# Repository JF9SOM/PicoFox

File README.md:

# PicoFox – A Hackable 2m Fox Transmitter

**PicoFox** is an open source fox transmitter for the 2-meter amateur band, built around the
RP2040 microcontroller (the same chip used in the Raspberry Pi Pico). It’s designed to be simple,
functional, and easy to modify.

PicoFox works well as a standalone fox for portable or walking hunts, but it’s also a great platform
for experimentation. There's ample CPU, flash, and GPIO available if you want to add features like
sensors or interactivity. The transmitter can generate a frequency or phase modulated signal with up
to 2.5kHz (data) bandwidth.

## Key Features
- Transmits FM in the 144–148 MHz band (ITU Zone 1: 144–146 MHz).
- Configured by editing a text file — no software or terminal needed.
- Transmits any 5kHz 16-bit PCM WAV file.
- Automatic Morse code ID with configurable tone, speed, and spacing.
- RF output > 18dBm at full power. Down to ~ -20dBm with full attenuation.
- Charges over USB.
- Expansion header provides:
  - 12 GPIOs (including I2C, SPI, UART, ADC).
  - Regulated 3.3V and raw battery voltage.
  - Two additional SI5351 clock outputs

### Getting One

Fully assembled PicoFox units are available from [AI6YM.radio](https://ai6ym.radio/picofox). An
enclosure, battery, and antenna are included. I ship nearly anywhere in the world.

You can also build your own - both the hardware and software are open source for non-commercial use.
For commercial inquiries, contact [justin@ai6ym.radio](mailto:justin@ai6ym.radio).

## Configuration

To configure your PicoFox, connect it to any computer using a micro USB cable. It will appear as a
USB mass storage device (like a flash drive). Open `settings.txt` with a text editor and adjust the
configuration values as needed. Eject the drive, disconnect USB, and power cycle the PicoFox to
apply the new settings.

To reset to factory settings, delete `settings.txt`, eject the drive, disconnect USB, and power
cycle the PicoFox. A default settings file will be regenerated.

### Settings Overview

- `CALLSIGN`: Alphanumeric callsign (max 12 characters).
- `ITU_ZONE`: ITU zone where the transmitter operates (`1`, `2`, or `3`).
- `FREQ_MHZ`: Transmit frequency in MHz.
- `ATTENUATION`: Attenuation level `0` - `127`, approximately 0.25dB steps.
- `DUTY_CYCLE`: Transmit duty cycle percentage (`0–100`).
- `MORSE_WPM`: Morse ID speed in words per minute.
- `MORSE_FARNSWORTH_WPM`: Slower Farnsworth spacing speed (ignored if lower than `MORSE_WPM`).
- `MORSE_TONE`: Morse tone frequency (100–2000 Hz).
- `MORSE_TONE_VOL`: Morse tone volume percentage (`1–100`).

**Note:** Invalid or missing values may disable the transmitter or revert to safe defaults.

## Using the Transmitter

After configuring settings as described above. The transmitter will turn on following the
provided settings the next time it is turned on.

The transmitter may be powered by an external USB power supply or the internal battery. The internal
battery charges over USB but no indication is available to show battery charging.

**Note: The power switch must be ON to charge the battery over USB. The transmitter will run on USB
power with the switch OFF but the battery will NOT be charged.**

A full battery will last about five hours at 100% duty cycle, 

## Replacing the Audio File

To change the audio transmission, replace the `audio.wav` file in the device’s flash storage. The
audio must be sampled at **5kHz**, **mono** (one channel), and encoded as **signed 16-bit PCM WAV**.

Using **Audacity** (free software available for all major OSs):

1. Set "Project Rate (Hz)" to `5000`.
2. Import, record, or generate your audio.
3. Mix down to a single mono track.
4. Export as WAV using **Signed 16-bit PCM** encoding.
5. Name the file `audio.wav` and copy it to the device.
6. Eject the drive and disconnect USB.
7. Power cycle the PicoFox.

**Notes:**

- Improper format may prevent audio transmission or cause noise to be transmitted instead.
- The audio is transmitted, followed by the morse ID, and then the transmitter turns off if
  `DUTY_CYCLE < 100`. In this way the length of the audio determines the transmit cycle time and the
  frequency of morse code ID transmissions. **YOU ARE RESPONSIBLE FOR COMPLYING WITH LOCAL LAWS FOR
  TRANSMITTING YOUR CALLSIGN!**
- To restore the default audio, delete `audio.wav`, eject the drive, disconnect USB, and power cycle
  the PicoFox.

## Design Brief

An SI5351 clock generator, locked to a TCXO, provides the RF signal. Modulation is applied in
software by the RP2040. To achieve smooth FM output, modulation is handled on core 1 with
I<sup>2</sup>C running at 1 MHz. Register writes are minimized and no other devices are on
I<sup>2</sup>C0.

Core 0 manages flash operations. Most extensions or new features should run on core 0.

**Note:** Mounting the device as a USB mass storage device will interrupt clean modulation as both
cores are blocked during flash operations.

The SPI flash device is split into program memory and a FAT16 filesystem. The filesystem contains
a text file for user-supplied settings, an audio file for transmission, a second audio file
containing the generated morse code ID, and a hash file used to detect changes to the settings file.
Unexpected files are automatically deleted and missing files are re-created from defaults in the
firmware binary.

The design intentionally includes large amounts of free CPU cycles, RAM, and flash so that cool
things can be built on the PicoFox.

## Development Guide

### Build Environment Setup

- Install Arduino IDE >= 2.3.
- Install libraries - Adafruit SPIFlash, Adafruit TinyUSB, Etherkit Si5351.
- Install board package from [my fork of Arduino-Pico](https://github.com/ai6ym/arduino-pico). This
  will be merged upstream eventually but for now you'll need the changes in my fork.
- In `Tools -> Board` select the `Raspberry Pi RP2040/RP2350 Boards -> AI6YM PicoFox`.
- Connect your PicoFox and select the appropriate TTY / COM port.

On Linux it may be necessary to add udev rules for this device. The relevant rules from my system
are below. I have no idea how this works on other operating systems. Mac is probably similar,
Windows should not be used for software developement of any kind (or really anything).

```
# Make an RP2040 in BOOTSEL mode writable by all users, so you can `picotool`
# without `sudo`. 
SUBSYSTEM=="usb", ATTRS{idVendor}=="2e8a", ATTRS{idProduct}=="0003", MODE="0666"

# Symlink an RP2040 running MicroPython from /dev/pico.
#
# Then you can `mpr connect $(realpath /dev/pico)`.
SUBSYSTEM=="tty", ATTRS{idVendor}=="2e8a", ATTRS{idProduct}=="0005", SYMLINK+="pico"

# Adafruit TinyUSB stack.
SUBSYSTEM=="tty", ATTRS{idVendor}=="239a", ATTRS{idProduct}=="cafe", MODE="0666"
SUBSYSTEM=="usb", ATTRS{idVendor}=="239a", ATTRS{idProduct}=="cafe", MODE="0666"
```

### Compilation Settings

- `Flash Size`: `16MB (Sketch: 1MB, FS: 15MB)`
- `CPU Speed`: `TBD`
- `USB Stack`: `Adafruit TinyUSB`

If needed for some reason you could change the partition layout to give more space for the sketch.
Doing so would destroy all data but the code automatically formats the partition and writes
defaults.

All other settings are fine at default values.

### Recovering a Board

In general the UF2 upload process will work fine. Click the upload button, after compilation the IDE
will push the board into UF2 update mode, write the new binary, and then reset the board to normal
operation.

If that doesn't work try the following:
- Reset the board and try again. Just tap the `RESET` button on the board to reset the RP2040.
- Force the device into `BOOTSEL` mode. Hold the `BOOTSEL` button, tap the `RESET` button, and then
  release the `BOOTSEL` button.
- Force the device into `BOOTSEL` mode **AND** change `Tools -> Upload Method` to `PicoTool`.
- When all else fails grab a PicoProbe (or a Pico / Pico2 flashed with the PicoProbe binary),
  connect that to the debug header of the PicoFox, and change `Tools -> Upload Method` to
  `Picoprobe`.
- If all of the above fails, well, he's dead Jim.

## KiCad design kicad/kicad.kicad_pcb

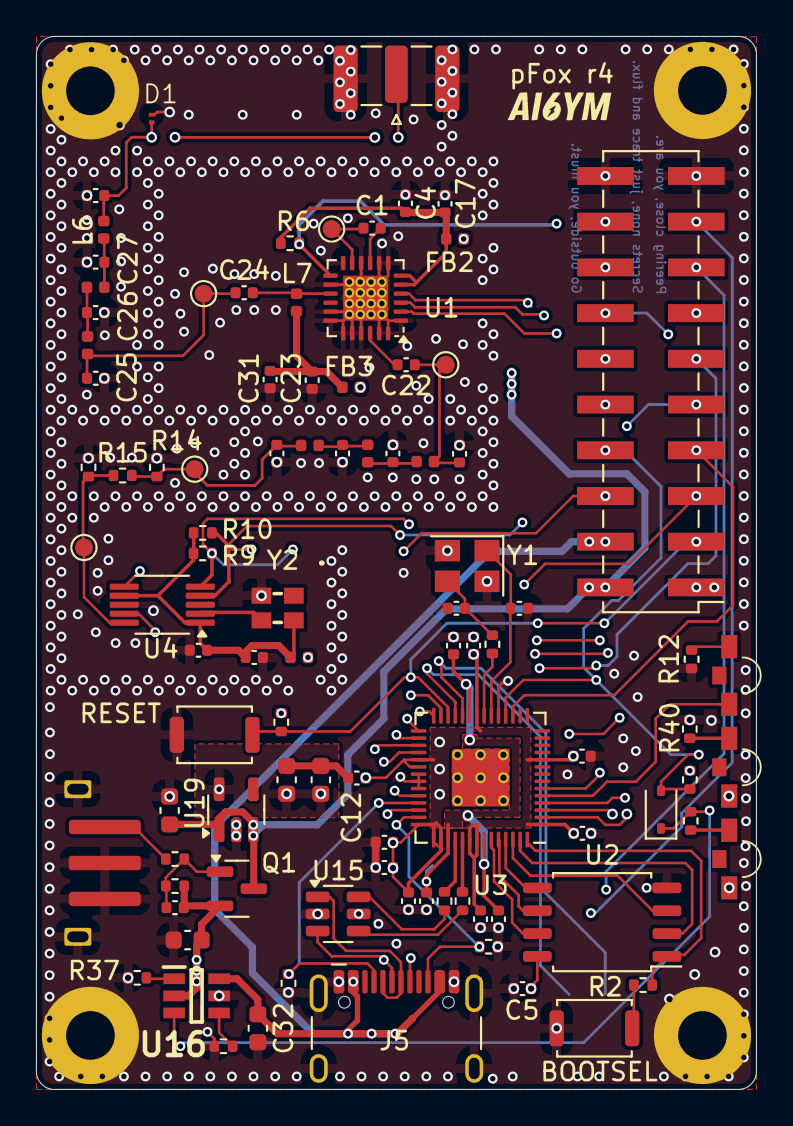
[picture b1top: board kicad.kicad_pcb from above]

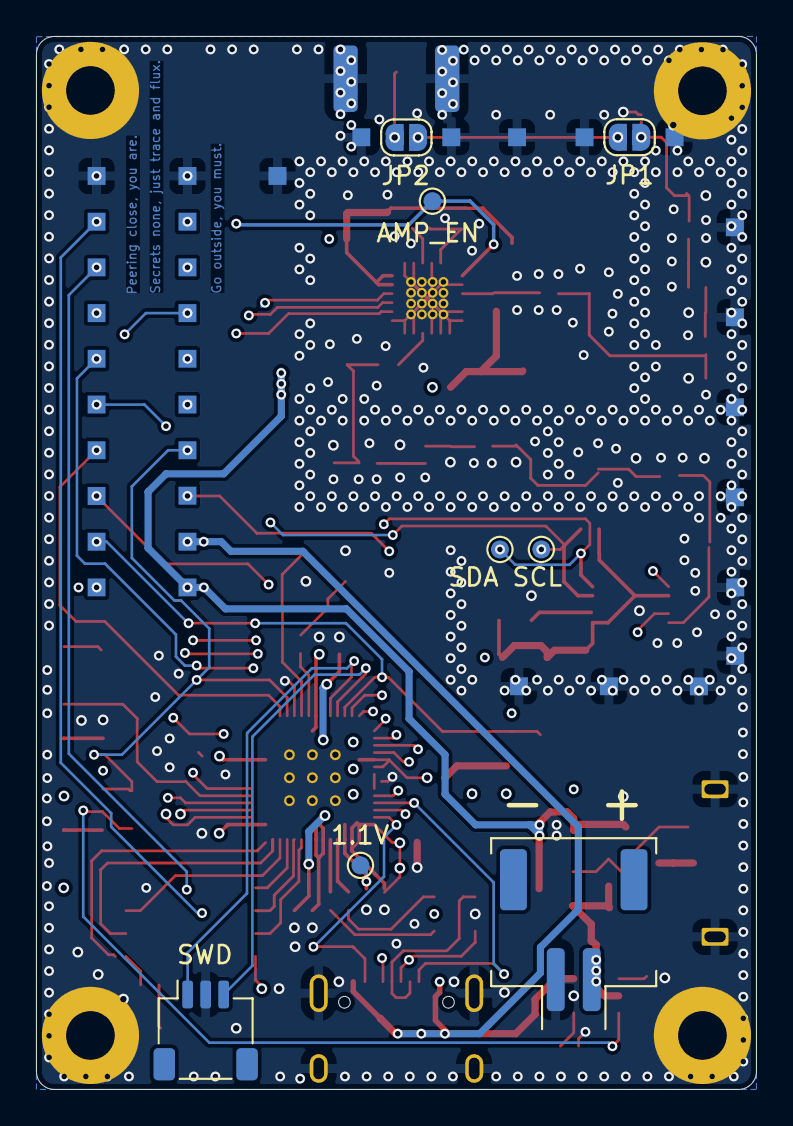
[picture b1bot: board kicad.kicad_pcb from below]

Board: 4 copper layers, 40.0 x 58.5 mm, 141 parts (43 on the bottom side), 71 nets.

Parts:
BT2: 3.7V; JST PH 2 Horizontal
C1, C22, C24: 10nF; C_0402_1005Metric
C2, C3: 15pF; C_0402_1005Metric
C4, C23, C68: 100pF; C_0402_1005Metric
C5, C6, C7, C9, C11, C12, C13, C14, C15, C16, C17, C31, C33, C67: 100nF; C_0402_1005Metric
C8, C10: 1uF; C_0402_1005Metric
C18, C21, C25, C28: 24pF; C_0402_1005Metric
C19, C20, C26, C27: 43pF; C_0402_1005Metric
C29, C30, C32, C40, C58: 10uF; C_0603_1608Metric
D1: H5VU06B; DFN0603-2L
D2, D4, D5: LED; LED 1206 Side View
D3: 1N4148WS; D_SOD-323
FB1, FB2, FB3: 600; L_0402_1005Metric
H1, H2, H3, H4: MountingHole; MountingHole_2.7mm_M2.5_Pad
J2: Conn_01x03_Pin; JST_SH_SM03B-SRSS-TB_1x03-1MP_P1.00mm_Horizontal
J3: Conn_02x10_Counter_Clockwise; PinHeader_2x10_P2.54mm_Vertical_SMD
J4: Conn_Coaxial_Small; SMA_Samtec_SMA-J-P-H-ST-EM1_EdgeMount
J5: USB-TYPE-C-018 (DEALON); USB_C_Receptacle_HCTL_HC-TYPE-C-16P-01A
JP1, JP2: SolderJumper_2_Open; SolderJumper-2_P1.3mm_Open_RoundedPad1.0x1.5mm
L1, L3, L4, L6: 68nH; L_0402_1005Metric
L2, L5: 75nH; L_0402_1005Metric
L7: 270nH; L_0402_1005Metric
Q1: AO3407A; SOT-23
R1: 100KR; R_0402_1005Metric
R2, R8, R37, R38: 10KR; R_0402_1005Metric
R3, R4: 33R; R_0402_1005Metric
R5, R6, R7, R36: 1KR; R_0402_1005Metric
R9, R10: 2.2KR; R_0402_1005Metric
R12, R40: 120R; R_0402_1005Metric
R13, R14, R39: 294R; R_0402_1005Metric
R15: 17.4R; R_0402_1005Metric
R27, R28: 5.11KR; R_0402_1005Metric
SW1, SW2: SW_Push_SPST_NO_Alps_SKRK
SW3: SK-12D15-G030; SW_Slide_SPDT_Angled_CK_OS102011MA1Q
TP1, TP2, TP3, TP4, TP5, TP6, TP7, TP8, TP9: TestPoint; TestPoint_Pad_D1.0mm
TP14, TP17, TP19, TP20, TP21, TP22, TP23, TP24, TP25, TP26, TP27, TP28, TP29, TP30, TP31, TP32, TP33, TP34, TP35, TP36, TP37, TP38, TP39, TP40, TP41, TP42, TP43, TP44, TP45, TP46, TP47, TP48, TP49, TP51, TP53: TestPoint; Castellation Pad
U1: BVA1761; QFN-24-1EP_4x4mm_P0.5mm_EP2.5x2.5mm
U2: W25Q128JVS; SOIC-8_5.23x5.23mm_P1.27mm
U3: RP2040; RP2040-QFN-56
U4: Si5351A-B-GT; MSOP-10_3x3mm_P0.5mm
U15: USBLC6-2SC6; SOT-23-6
U16: BQ21040DBVR; SOT95P280X145-6N
U19: ME6217C33M5G; SOT-23-5
Y1: ABM8-272-T3; Crystal_SMD_3225-4Pin_3.2x2.5mm
Y2: TG2016SMN_25.0000M-MCGNNM0; TG2016SMN250000MMCGNNM0

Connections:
+1V1: C6.1, C7.1, C8.1, TP3.1, U3.23 (DVDD), U3.45 (VREG_VOUT), U3.50 (DVDD)
+3V3: C5.1, C9.1, C10.1, C11.1, C12.1, C13.1, C14.1, C15.1, C16.1, C30.1, C40.1, D5.1 (A), FB1.1, FB2.1, J3.1, R8.2, R38.1, TP14.1, U2.8 (VCC), U3.1 (IOVDD), U3.10 (IOVDD), U3.22 (IOVDD), U3.33 (IOVDD), U3.34 (GPIO22), U3.42 (IOVDD), U3.43 (ADC_AVDD), U3.44 (VREG_IN), U3.48 (USB_VDD), U3.49 (IOVDD), U19.5 (V_{OUT})
+BATT: BT2.1 (+), C29.1, C33.2, Q1.2 (S), R1.1, U16.2 (OUT)
/AMP_EN: R6.1, TP6.1, U1.13 (AEN), U3.4 (GPIO2)
/ATTN_LE: U1.2 (LE), U3.6 (GPIO4)
/CC1Sense: J3.16, J5.A5 (CC1), R28.1, TP29.1, U3.39 (GPIO27_ADC1)
/CC2Sense: J3.18, J5.B5 (CC2), R27.1, TP28.1, U3.41 (GPIO29_ADC3)
/CLK1: J3.5, TP19.1, U4.9 (CLK1)
/CLK2: J3.6, TP34.1, U4.6 (CLK2)
/ChgSense: D3.2 (A), J3.8, R38.2, TP33.1, U3.18 (GPIO15)
/GPIO14: J3.7, TP20.1, U3.17 (GPIO14)
/GPIO16: J3.9, TP21.1, U3.27 (GPIO16)
/GPIO17: J3.10, TP32.1, U3.28 (GPIO17)
/GPIO18: J3.11, TP22.1, U3.29 (GPIO18)
/GPIO19: J3.12, TP31.1, U3.30 (GPIO19)
/GPIO20: J3.13, TP23.1, U3.31 (GPIO20)
/GPIO21: J3.14, TP30.1, U3.32 (GPIO21)
/GPIO26_ADC0: J3.15, TP26.1, U3.38 (GPIO26_ADC0)
/GPIO28_ADC2: J3.17, TP25.1, U3.40 (GPIO28_ADC2)
/I2C0 SCL: R10.1, TP5.1, U1.3 (CLK), U3.3 (GPIO1), U4.4 (SCL)
/I2C0 SDA: R9.1, TP4.1, U1.4 (DATA), U3.2 (GPIO0), U4.5 (SDA)
/QSPI_SCLK: U2.6 (CLK), U3.52 (QSPI_SCLK)
/QSPI_SD0: U2.5 (DI(IO0)), U3.53 (QSPI_SD0)
/QSPI_SD1: U2.2 (DO(IO1)), U3.55 (QSPI_SD1)
/QSPI_SD2: U2.3 (IO2), U3.54 (QSPI_SD2)
/QSPI_SD3: U2.7 (IO3), U3.51 (QSPI_SD3)
/QSPI_SS: R2.2, U2.1 (~CS), U3.56 (QSPI_SS)
/RUN: J3.3, R8.1, SW1.2, TP17.1, U3.26 (RUN)
/SWCLK: J2.1, U3.24 (SWCLK)
/SWD: J2.3, U3.25 (SWD)
/SWITCHED_VBATT: C58.1, FB3.1, J3.2, Q1.3 (D), TP36.1, U19.1 (V_{IN}), U19.3 (CE)
/USB ESD D+: J5.A6 (D+), J5.B6 (D+), U15.3 (I/O2)
/USB ESD D-: J5.A7 (D-), J5.B7 (D-), U15.1 (I/O1)
/USB_D+: R3.1, U15.4 (I/O2)
/USB_D-: R4.1, U15.6 (I/O1)
/XIN: C2.1, U3.20 (XIN), Y1.1
/XOUT: R5.1, U3.21 (XOUT)
/~USB_BOOT: R2.1, SW2.2
GND: BT2.2 (-), C2.2, C3.2, C4.1, C5.2, C6.2, C7.2, C8.2, C9.2, C10.2, C11.2, C12.2, C13.2, C14.2, C15.2, C16.2, C17.1, C18.2, C19.2, C20.2, C21.2, C23.1, C25.2, C26.2, C27.2, C28.2, C29.2, C30.2, C31.1, C32.2, C40.2, C58.2, C67.1, C68.1, D1.1 (A1), H1.1, H2.1, H3.1, H4.1, J2.2, J3.19, J3.20, J4.2 (Ext), J5.A1 (GND), J5.A12 (GND), J5.B1 (GND), J5.B12 (GND), J5.S1 (SHIELD), R12.2, R13.2, R14.2, R27.2, R28.2, R36.2, R37.2, R40.1, SW1.1, SW2.1, SW3.2 (B), SW3.3 (C), SW3.4 (SH), SW3.5 (SH), TP24.1, TP27.1, TP37.1, TP38.1, TP39.1, TP40.1, TP41.1, TP42.1, TP43.1, TP44.1, TP45.1, TP46.1, TP47.1, TP48.1, TP49.1, TP51.1, TP53.1, U1.1 (A1), U1.7 (A0), U1.8 (GND), U1.10 (GND), U1.12 (GND), U1.14 (GND), U1.17 (GND), U1.18 (GND), U1.19 (GND), U1.20 (GND), U1.21 (GND), U1.23 (GND), U1.24 (A2), U1.25 (PAD), U2.4 (GND), U3.19 (TESTEN), U3.35 (GPIO23), U3.36 (GPIO24), U3.37 (GPIO25), U3.57 (GND), U4.8 (GND), U15.2 (GND), U16.5 (GND), U19.2 (V_{SS}), Y1.2, Y1.4, Y2.2 (GND)
unnamed: C3.1, R5.2, Y1.3
unnamed: C18.1, L1.1, R14.1, R15.2, TP2.1
unnamed: C19.1, L1.2, L2.1
unnamed: C20.1, L2.2, L3.1
unnamed: C21.1, C22.1, L3.2, TP8.1
unnamed: C23.2, C31.2, FB3.2, L7.2
unnamed: C24.2, C25.1, L4.1, TP9.1
unnamed: C26.1, L4.2, L5.1
unnamed: C27.1, L5.2, L6.1
unnamed: C28.1, D1.2 (A2), JP1.1 (A), L6.2
unnamed: D2.1 (A), U3.5 (GPIO3)
unnamed: D2.2 (K), R12.1
unnamed: D3.1 (K), R39.1, U16.3 (~CHG)
unnamed: D4.2 (K), R39.2
unnamed: D5.2 (K), R40.2
unnamed: J4.1 (In), JP2.2 (B)
unnamed: JP1.2 (B), JP2.1 (A)
unnamed: C33.1, Q1.1 (G), R1.2, R7.1
unnamed: R7.2, SW3.1 (A)
unnamed: C4.2, C17.2, FB2.2, R6.2, U1.5 (DSAVDD), U1.6 (P/S)
unnamed: C22.2, U1.22 (RF1)
unnamed: C1.1, U1.9 (RF2)
unnamed: C1.2, TP1.1, U1.11 (RF3)
unnamed: C24.1, L7.1, U1.15 (RF4)
unnamed: R4.2, U3.46 (USB_DM)
unnamed: R3.2, U3.47 (USB_DP)
unnamed: R13.1, R15.1, TP7.1, U4.10 (CLK0)
unnamed: C67.2, C68.2, FB1.2, R9.2, R10.2, U4.1 (VDD), U4.7 (VDDO), Y2.4 (VCC)
unnamed: U4.2 (XA), Y2.3 (OUT)
unnamed: R36.1, U16.4 (ISET)
unnamed: R37.1, U16.1 (TS)
VBUS: C32.1, D4.1 (A), J3.4, J5.A4 (VBUS), J5.A9 (VBUS), J5.B4 (VBUS), J5.B9 (VBUS), TP35.1, U15.5 (VBUS), U16.6 (VIN)

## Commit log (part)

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2026-04-16 PicoFox r3
2026-06-28 docs: add ordering guide with suppliers and tips
2026-06-28 docs: fix regulatory note to reflect JARD certification for homebuilt transceivers
